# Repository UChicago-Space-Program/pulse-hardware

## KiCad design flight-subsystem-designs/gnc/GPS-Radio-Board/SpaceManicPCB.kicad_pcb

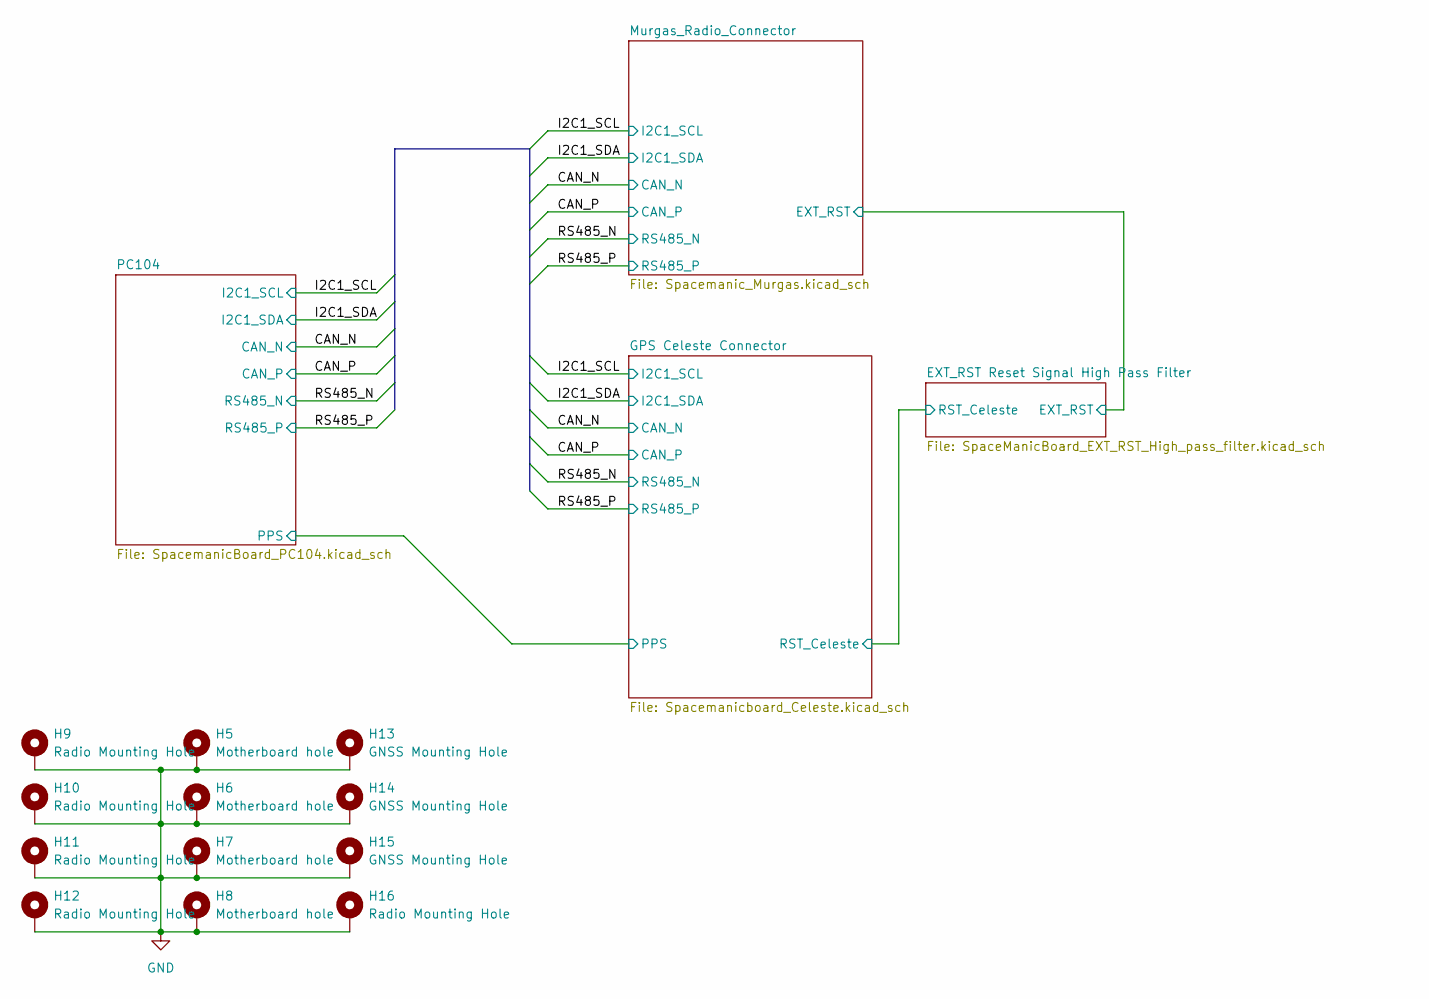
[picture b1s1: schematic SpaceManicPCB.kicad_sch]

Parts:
H5, H6, H7, H8: Motherboard hole; MountingHole_3.2mm_M3_DIN965_Pad_TopBottom
H9, H10, H11, H12, H16: Radio Mounting Hole; MountingHole_2.5mm
H13, H14, H15: GNSS Mounting Hole; MountingHole_2.5mm

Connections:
GND: H5.1, H6.1, H7.1, H8.1, H9.1, H10.1, H11.1, H12.1, H13.1, H14.1, H15.1, H16.1; also elsewhere on the board

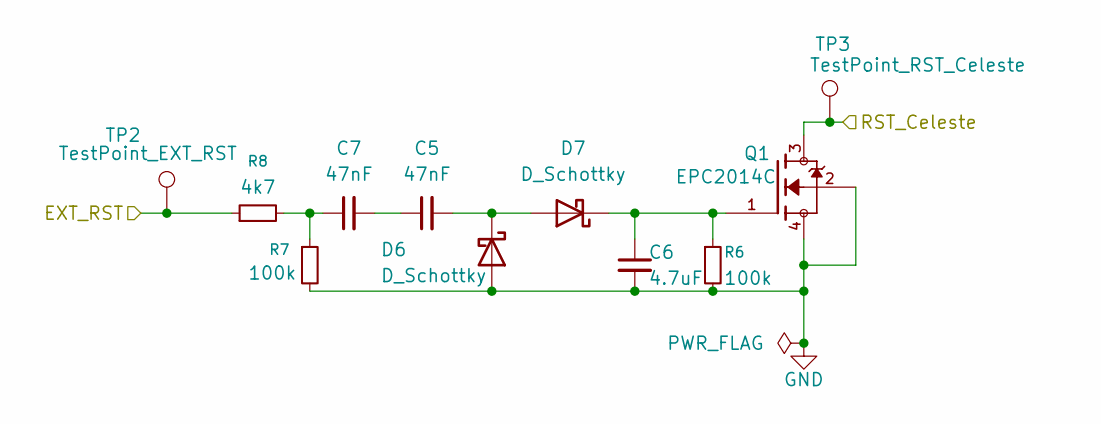
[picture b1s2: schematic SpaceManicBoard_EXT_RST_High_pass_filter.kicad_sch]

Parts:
C5, C7: 47nF; C_0603_1608Metric
C6: 4.7uF; C_0603_1608Metric
D6, D7: D_Schottky; D_0402_1005Metric
Q1: EPC2014C; TRANS_EPC2014C; PARTREV N/A
R6, R7: 100k; R_0603_1608Metric
R8: 4k7; R_0402_1005Metric
TP2: TestPoint_EXT_RST; TestPoint_Pad_D1.5mm
TP3: TestPoint_RST_Celeste; TestPoint_Pad_D1.5mm

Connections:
/EXT_RST Reset Signal High Pass Filter/EXT_RST: R8.1, TP2.1; also elsewhere on the board
/EXT_RST Reset Signal High Pass Filter/RST_Celeste: Q1.3, Q1.5, TP3.1; also elsewhere on the board
GND: C6.2, D6.2 (A), Q1.2, Q1.4, R6.2, R7.2; also elsewhere on the board
unnamed: C5.1, C7.2
unnamed: C7.1, R7.1, R8.2
unnamed: C5.2, D6.1 (K), D7.2 (A)
unnamed: C6.1, D7.1 (K), Q1.1, R6.1

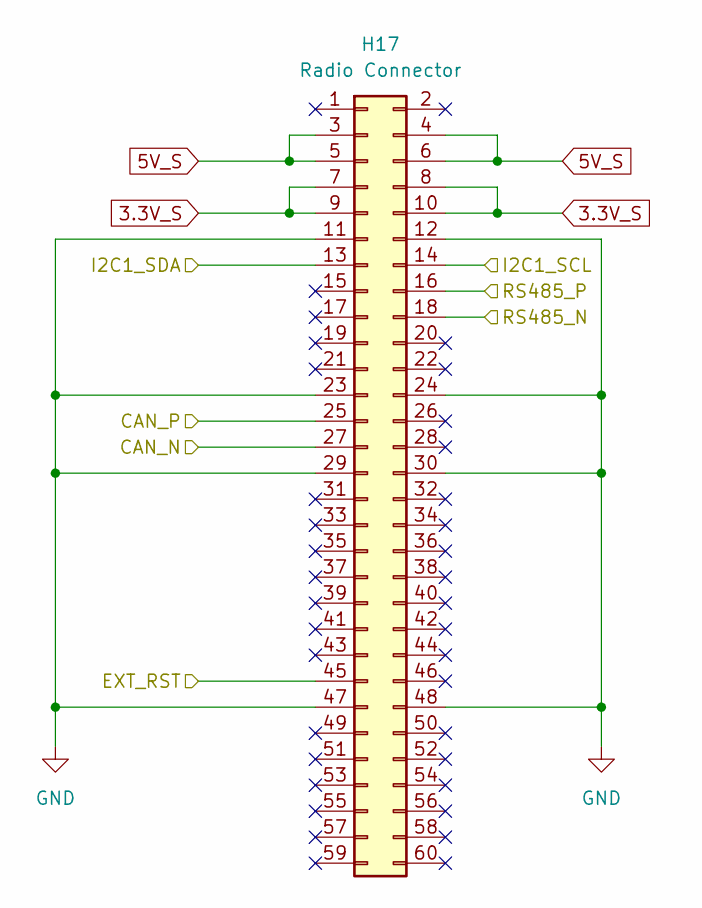
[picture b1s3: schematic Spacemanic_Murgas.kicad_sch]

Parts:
H17: Radio Connector; CON_MolexSlimStack_54363-0689

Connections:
3.3V_S: H17.7, H17.8, H17.9, H17.10; also elsewhere on the board
5V_S: H17.3, H17.4, H17.5, H17.6; also elsewhere on the board
/CAN_N: H17.27; also elsewhere on the board
/CAN_P: H17.25; also elsewhere on the board
/EXT_RST Reset Signal High Pass Filter/EXT_RST: H17.45; also elsewhere on the board
/I2C1_SCL: H17.14; also elsewhere on the board
/I2C1_SDA: H17.13; also elsewhere on the board
/RS485_N: H17.18; also elsewhere on the board
/RS485_P: H17.16; also elsewhere on the board
GND: H17.11, H17.12, H17.23, H17.24, H17.29, H17.30, H17.47, H17.48; also elsewhere on the board

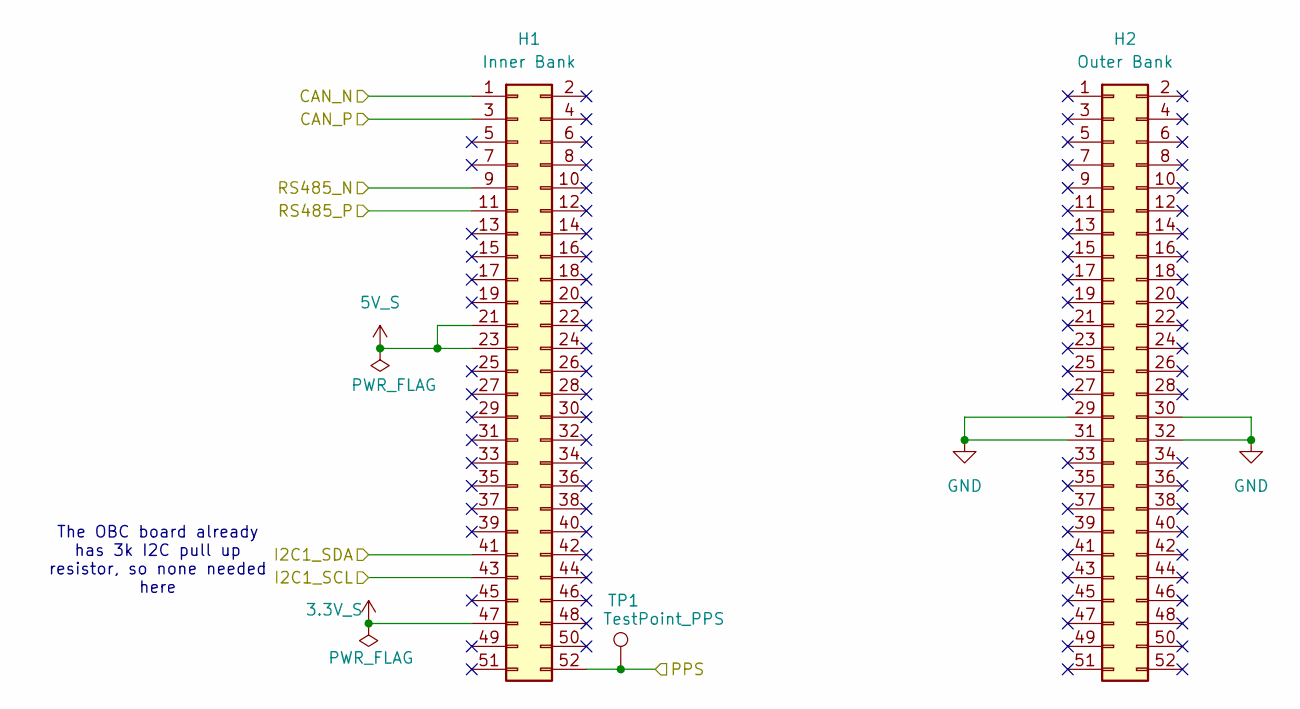
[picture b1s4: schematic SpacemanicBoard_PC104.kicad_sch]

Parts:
H1: Inner Bank; PinHeader_2x26_P2.54mm_Vertical
H2: Outer Bank; PinHeader_2x26_P2.54mm_Vertical
TP1: TestPoint_PPS; TestPoint_Pad_D1.5mm

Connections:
3.3V_S: H1.47; also elsewhere on the board
5V_S: H1.21, H1.23; also elsewhere on the board
/CAN_N: H1.1; also elsewhere on the board
/CAN_P: H1.3; also elsewhere on the board
/GPS Celeste Connector/PPS: H1.52, TP1.1; also elsewhere on the board
/I2C1_SCL: H1.43; also elsewhere on the board
/I2C1_SDA: H1.41; also elsewhere on the board
/RS485_N: H1.9; also elsewhere on the board
/RS485_P: H1.11; also elsewhere on the board
GND: H2.29, H2.30, H2.31, H2.32; also elsewhere on the board

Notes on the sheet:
The OBC board already has 3k I2C pull up resistor, so none needed here

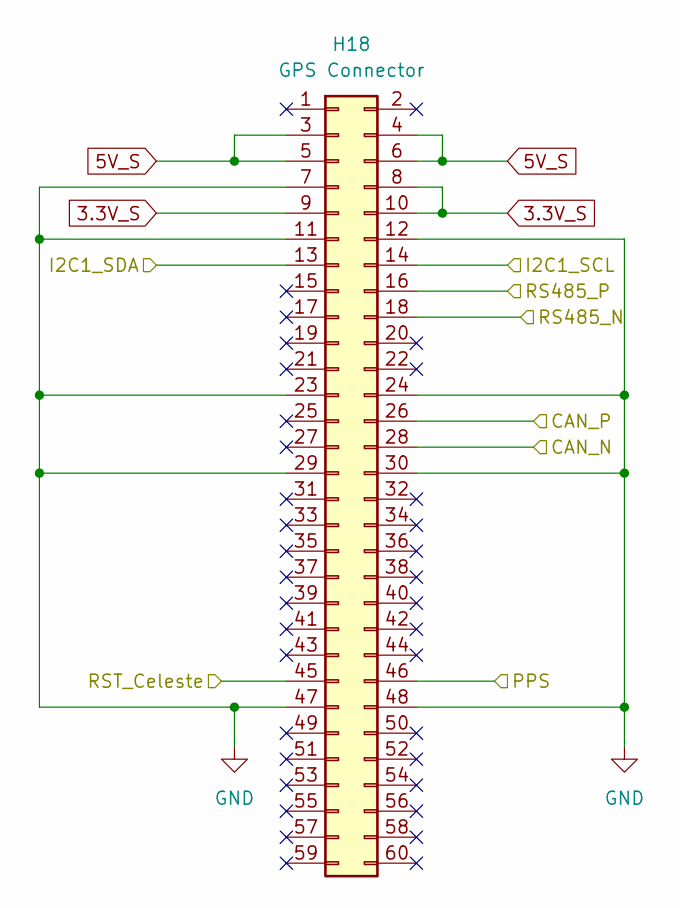
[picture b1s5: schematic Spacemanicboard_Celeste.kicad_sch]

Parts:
H18: GPS Connector; CON_MolexSlimStack_54363-0689

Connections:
3.3V_S: H18.8, H18.9, H18.10; also elsewhere on the board
5V_S: H18.3, H18.4, H18.5, H18.6; also elsewhere on the board
/CAN_N: H18.28; also elsewhere on the board
/CAN_P: H18.26; also elsewhere on the board
/EXT_RST Reset Signal High Pass Filter/RST_Celeste: H18.45; also elsewhere on the board
/GPS Celeste Connector/PPS: H18.46; also elsewhere on the board
/I2C1_SCL: H18.14; also elsewhere on the board
/I2C1_SDA: H18.13; also elsewhere on the board
/RS485_N: H18.18; also elsewhere on the board
/RS485_P: H18.16; also elsewhere on the board
GND: H18.7, H18.11, H18.12, H18.23, H18.24, H18.29, H18.30, H18.47, H18.48; also elsewhere on the board

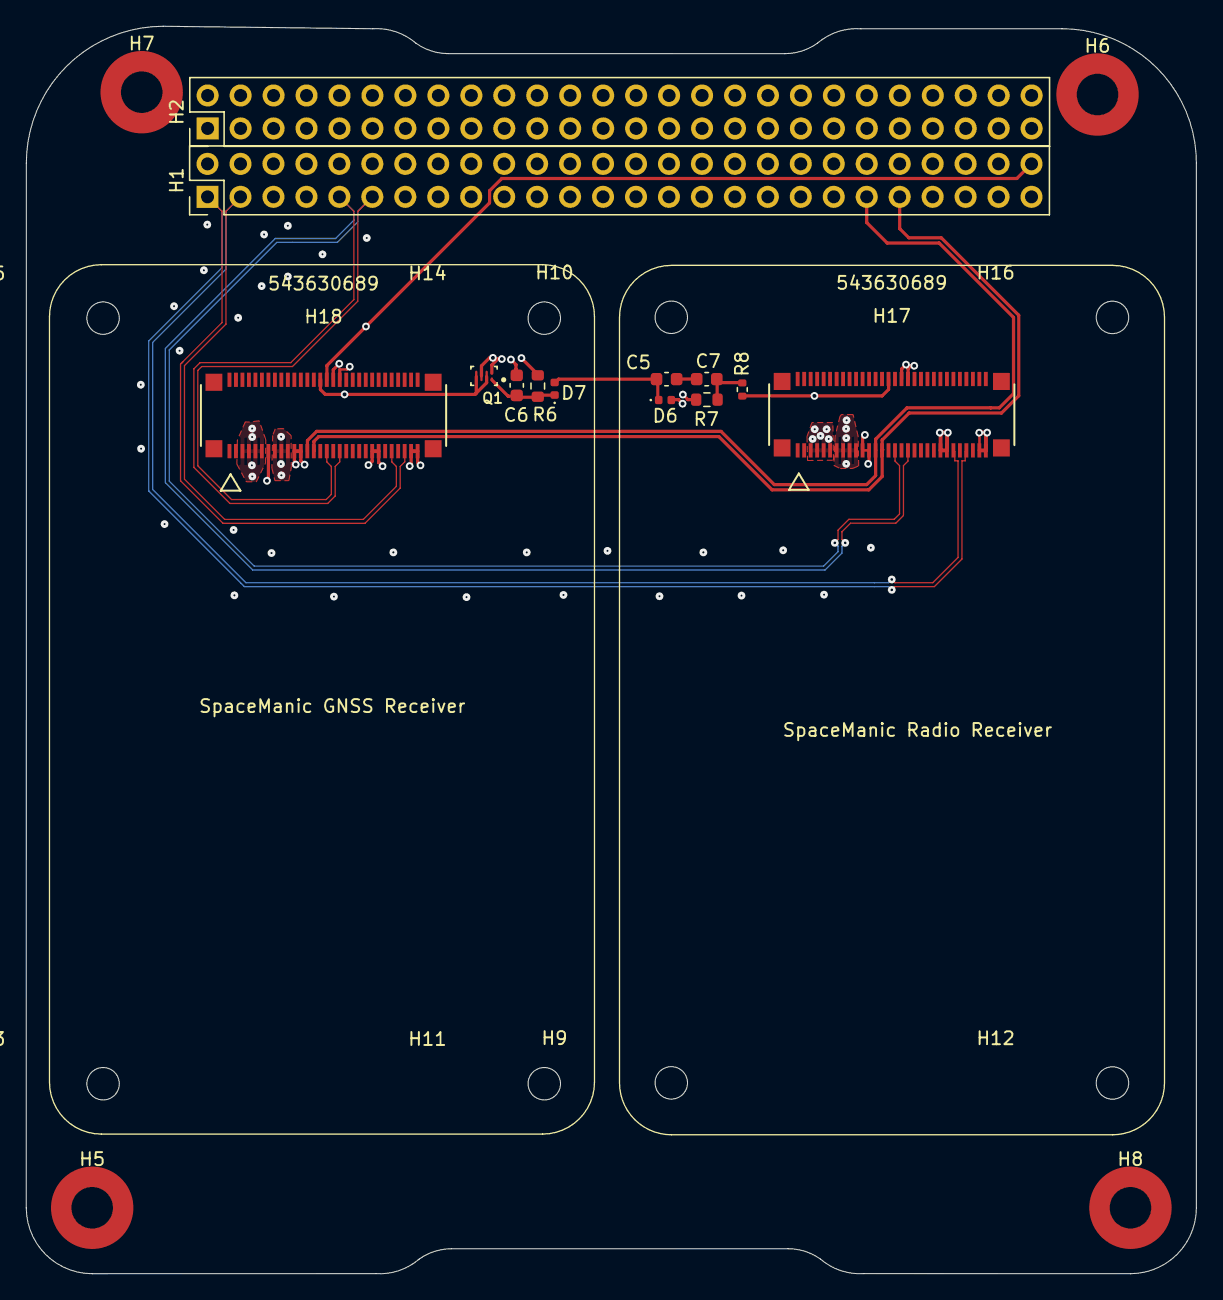
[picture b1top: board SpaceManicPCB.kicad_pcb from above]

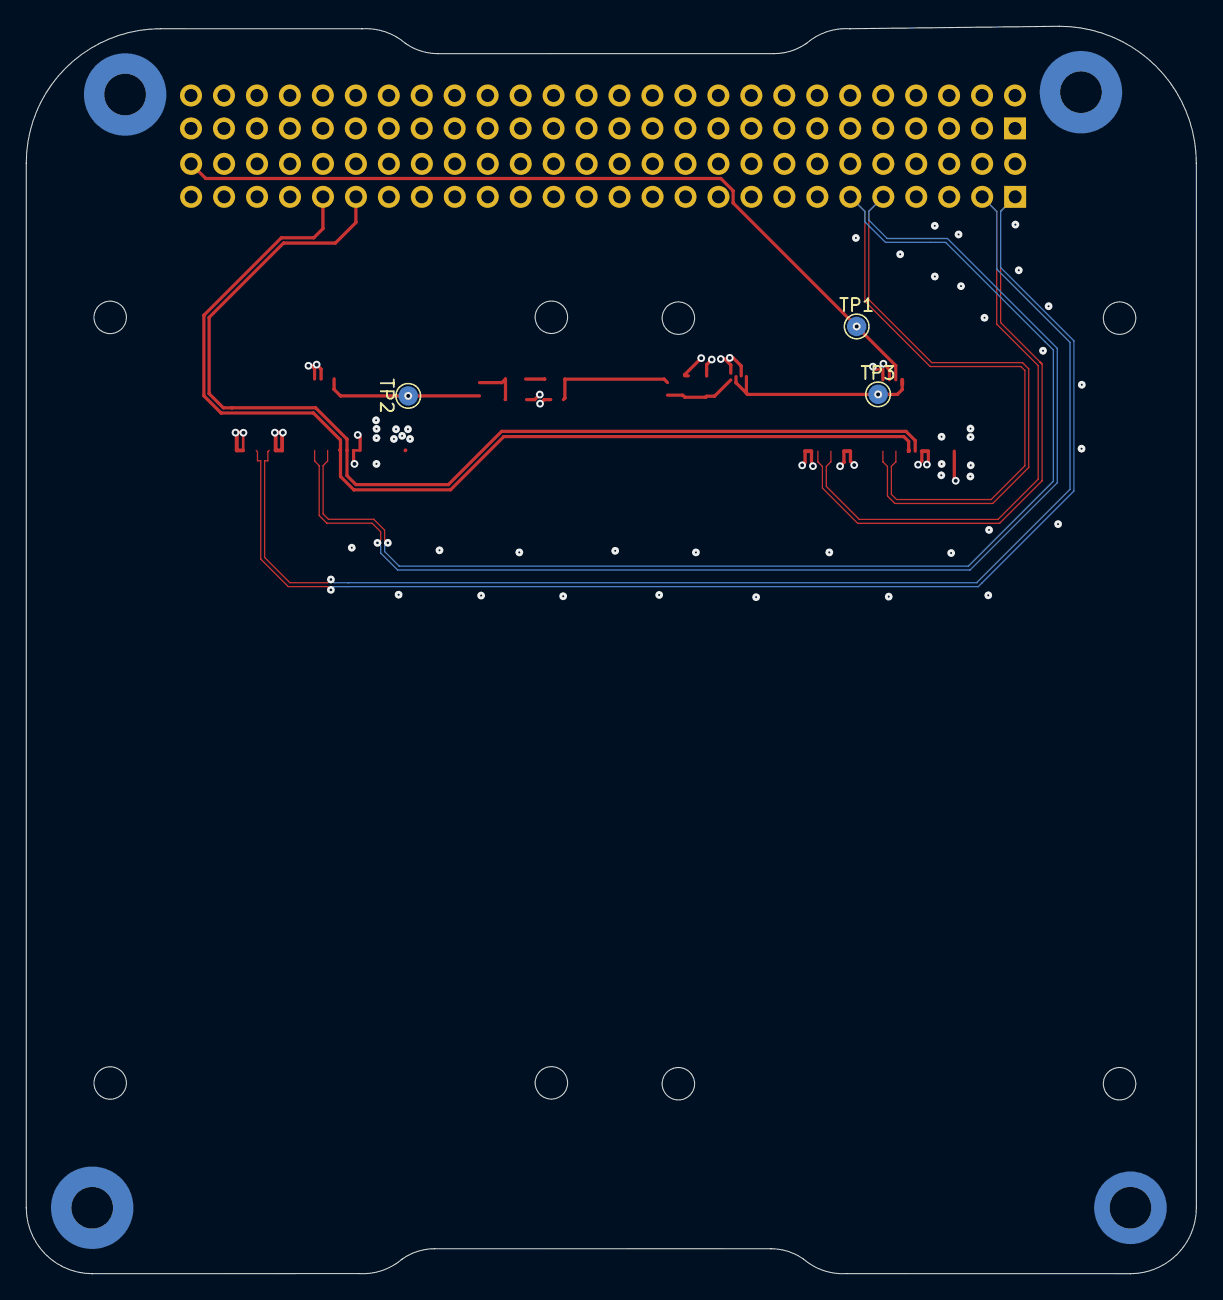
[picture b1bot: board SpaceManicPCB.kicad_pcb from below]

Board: 4 copper layers, 90.2 x 96.1 mm, 28 parts (3 on the bottom side), 16 nets.

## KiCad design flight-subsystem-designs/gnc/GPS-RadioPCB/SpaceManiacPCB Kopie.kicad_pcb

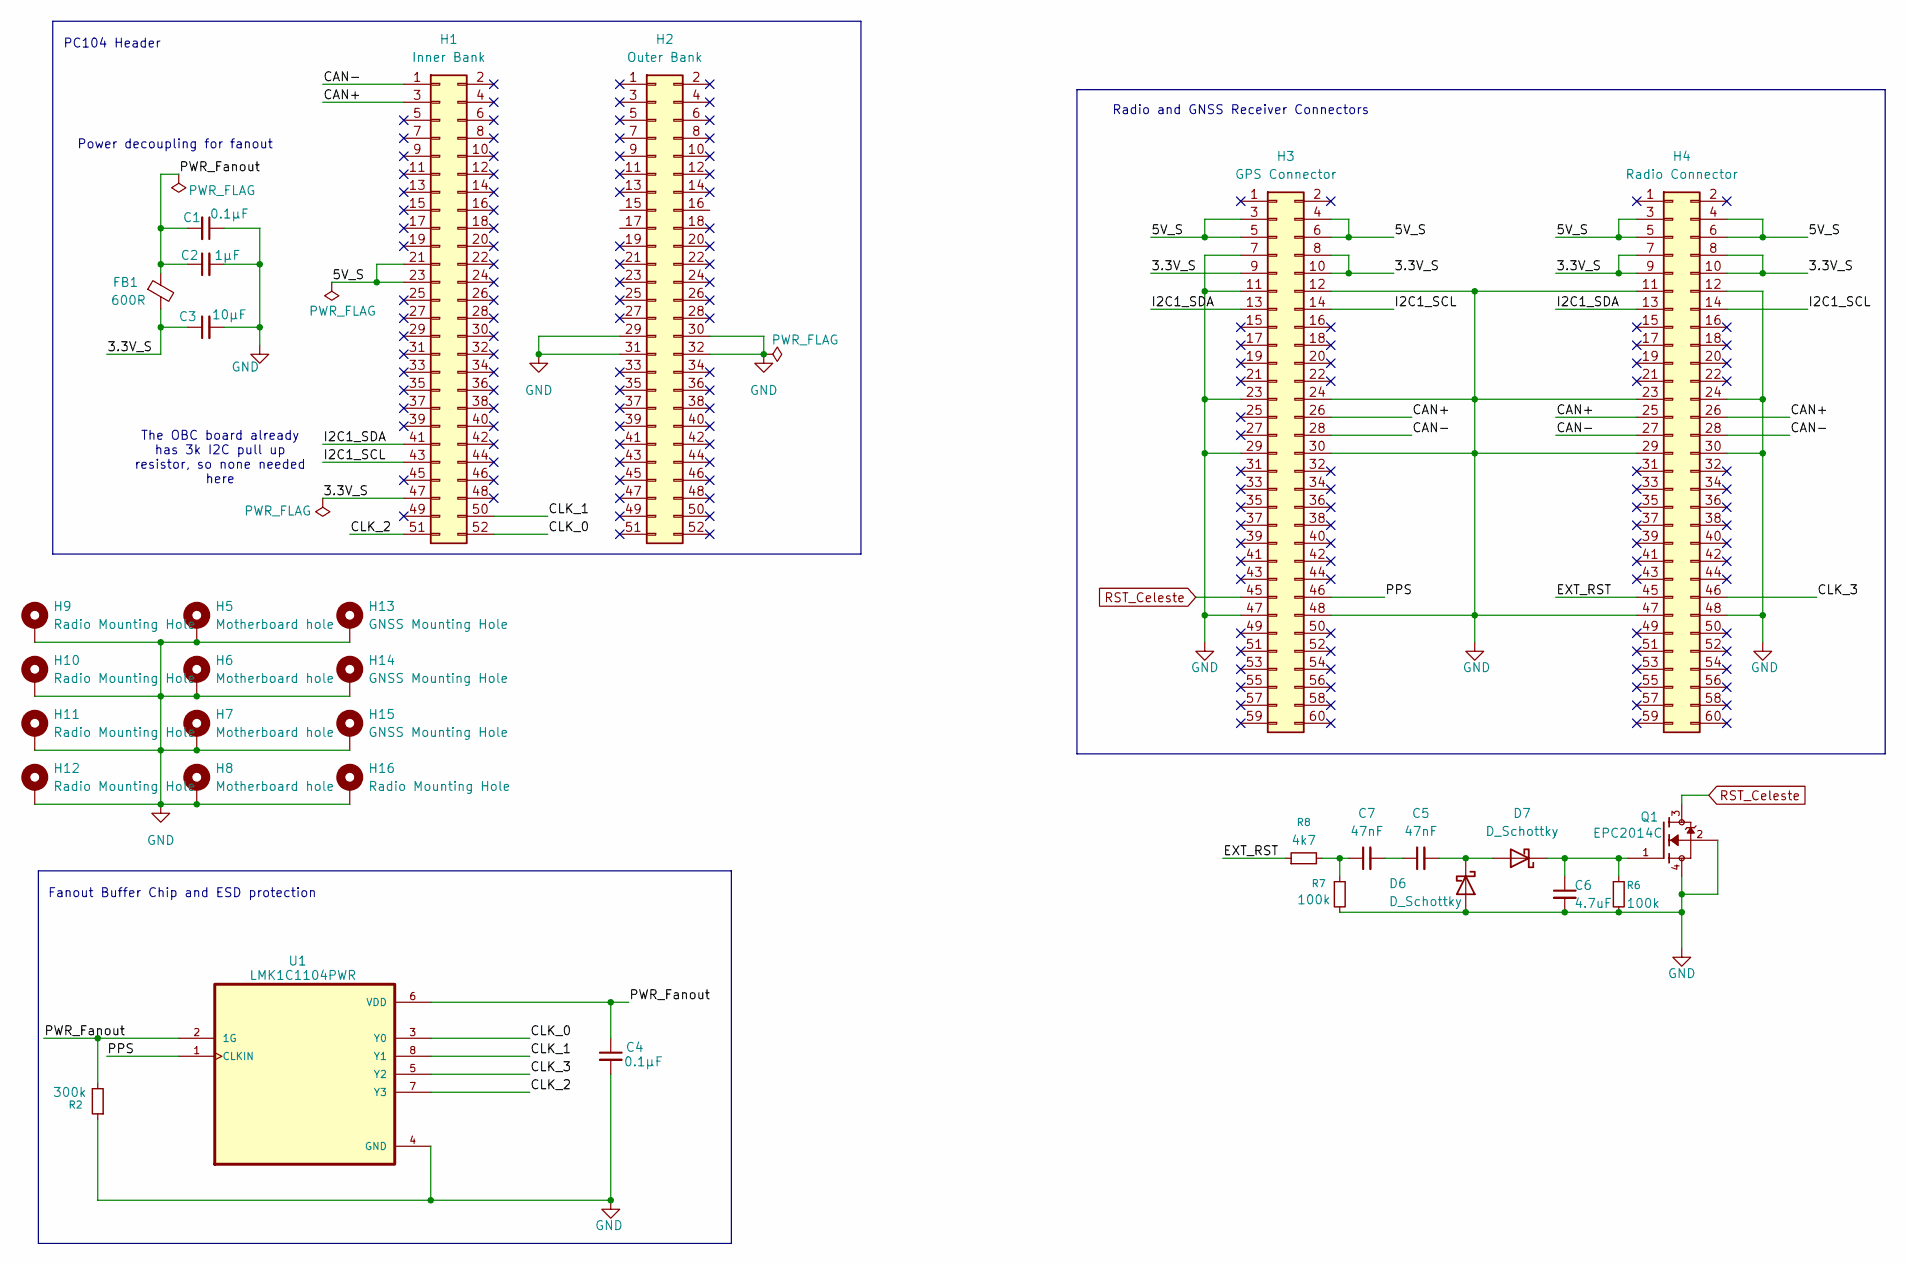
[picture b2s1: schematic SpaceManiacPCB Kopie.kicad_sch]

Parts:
C1, C4: 0.1μF; C_0402_1005Metric
C2: 1μF; C_0402_1005Metric
C3: 10μF; C_0402_1005Metric
C5, C7: 47nF; C_0603_1608Metric
C6: 4.7uF; C_0603_1608Metric
D6, D7: D_Schottky; D_0402_1005Metric
FB1: 600R; L_0603_1608Metric
H1: Inner Bank; PinHeader_2x26_P2.54mm_Vertical
H2: Outer Bank; PinHeader_2x26_P2.54mm_Vertical
H3: GPS Connector; CON_MolexSlimStack_54363-0689
H4: Radio Connector; CON_MolexSlimStack_54363-0689
H5, H6, H7, H8: Motherboard hole; MountingHole_3.2mm_M3_DIN965_Pad_TopBottom
H9, H10, H11, H12, H16: Radio Mounting Hole; MountingHole_3.2mm_M3_DIN965_Pad_TopBottom
H13, H14, H15: GNSS Mounting Hole; MountingHole_3.2mm_M3_DIN965_Pad_TopBottom
Q1: EPC2014C; TRANS_EPC2014C; PARTREV N/A
R2: 300k; R_0402_1005Metric
R6, R7: 100k; R_0402_1005Metric
R8: 4k7; R_0402_1005Metric
U1: LMK1C1104PWR; SOP65P640X120-8N; DigiKey_Part_Number 296-LMK1C1104PWRTR-ND

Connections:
/3.3V_S: C3.1, FB1.2, H1.47, H3.8, H3.9, H3.10, H4.7, H4.8, H4.9, H4.10
/5V_S: H1.21, H1.23, H3.3, H3.4, H3.5, H3.6, H4.3, H4.4, H4.5, H4.6
/CAN+: H1.3, H3.26, H4.25, H4.26
/CAN-: H1.1, H3.28, H4.27, H4.28
/CLK_0: H1.52, U1.3 (Y0)
/CLK_1: H1.50, U1.8 (Y1)
/CLK_2: H1.51, U1.7 (Y3)
/CLK_3: H4.46, U1.5 (Y2)
/EXT_RST: H4.45, R8.1
/I2C1_SCL: H1.43, H3.14, H4.14
/I2C1_SDA: H1.41, H3.13, H4.13
/PPS: H3.46, U1.1 (CLKIN)
/PWR_Fanout: C1.2, C2.1, C4.1, FB1.1, R2.2, U1.2 (1G), U1.6 (VDD)
GND: C1.1, C2.2, C3.2, C4.2, C6.2, D6.2 (A), H2.29, H2.30, H2.31, H2.32, H3.7, H3.11, H3.12, H3.23, H3.24, H3.29, H3.30, H3.47, H3.48, H4.11, H4.12, H4.23, H4.24, H4.29, H4.30, H4.47, H4.48, H5.1, H6.1, H7.1, H8.1, H9.1, H10.1, H11.1, H12.1, H13.1, H14.1, H15.1, H16.1, Q1.2, Q1.4, R2.1, R6.2, R7.2, U1.4 (GND)
unnamed: C5.1, C7.2
unnamed: C7.1, R7.1, R8.2
unnamed: C5.2, D6.1 (K), D7.2 (A)
unnamed: C6.1, D7.1 (K), Q1.1, R6.1
RST_Celeste: H3.45, Q1.3, Q1.5

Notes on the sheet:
PC104 Header
The OBC board already has 3k I2C pull up resistor, so none needed here
Fanout Buffer Chip and ESD protection
Power decoupling for fanout
Radio and GNSS Receiver Connectors

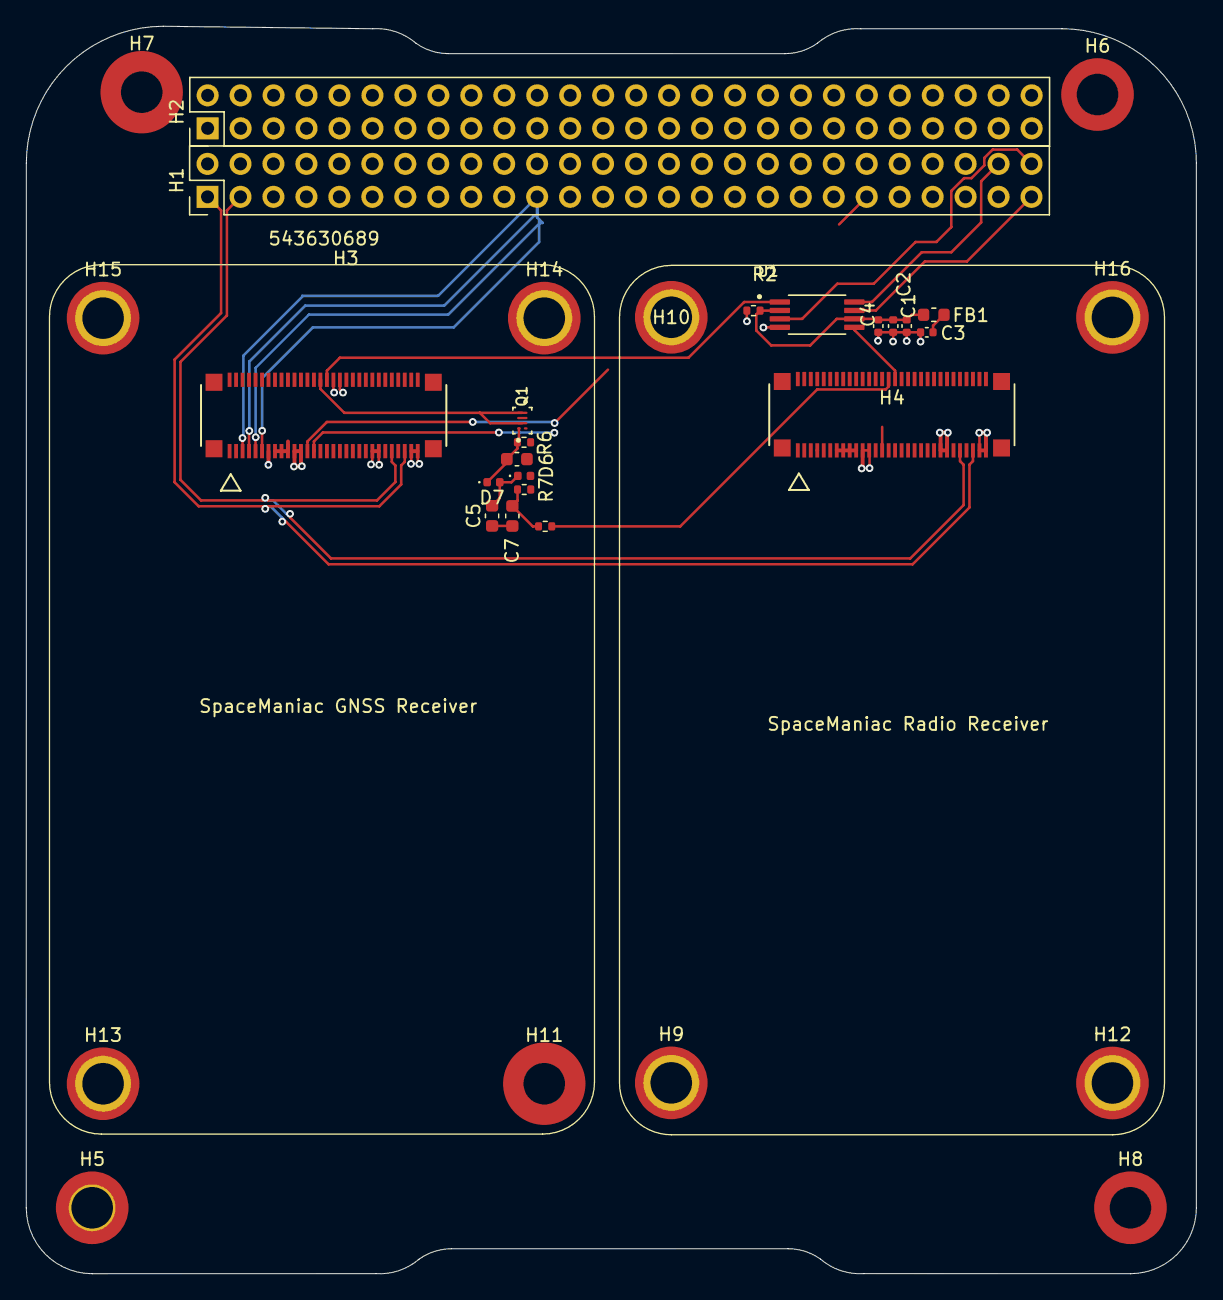
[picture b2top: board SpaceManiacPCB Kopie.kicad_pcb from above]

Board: 2 copper layers, 90.2 x 96.1 mm, 32 parts (0 on the bottom side), 19 nets.

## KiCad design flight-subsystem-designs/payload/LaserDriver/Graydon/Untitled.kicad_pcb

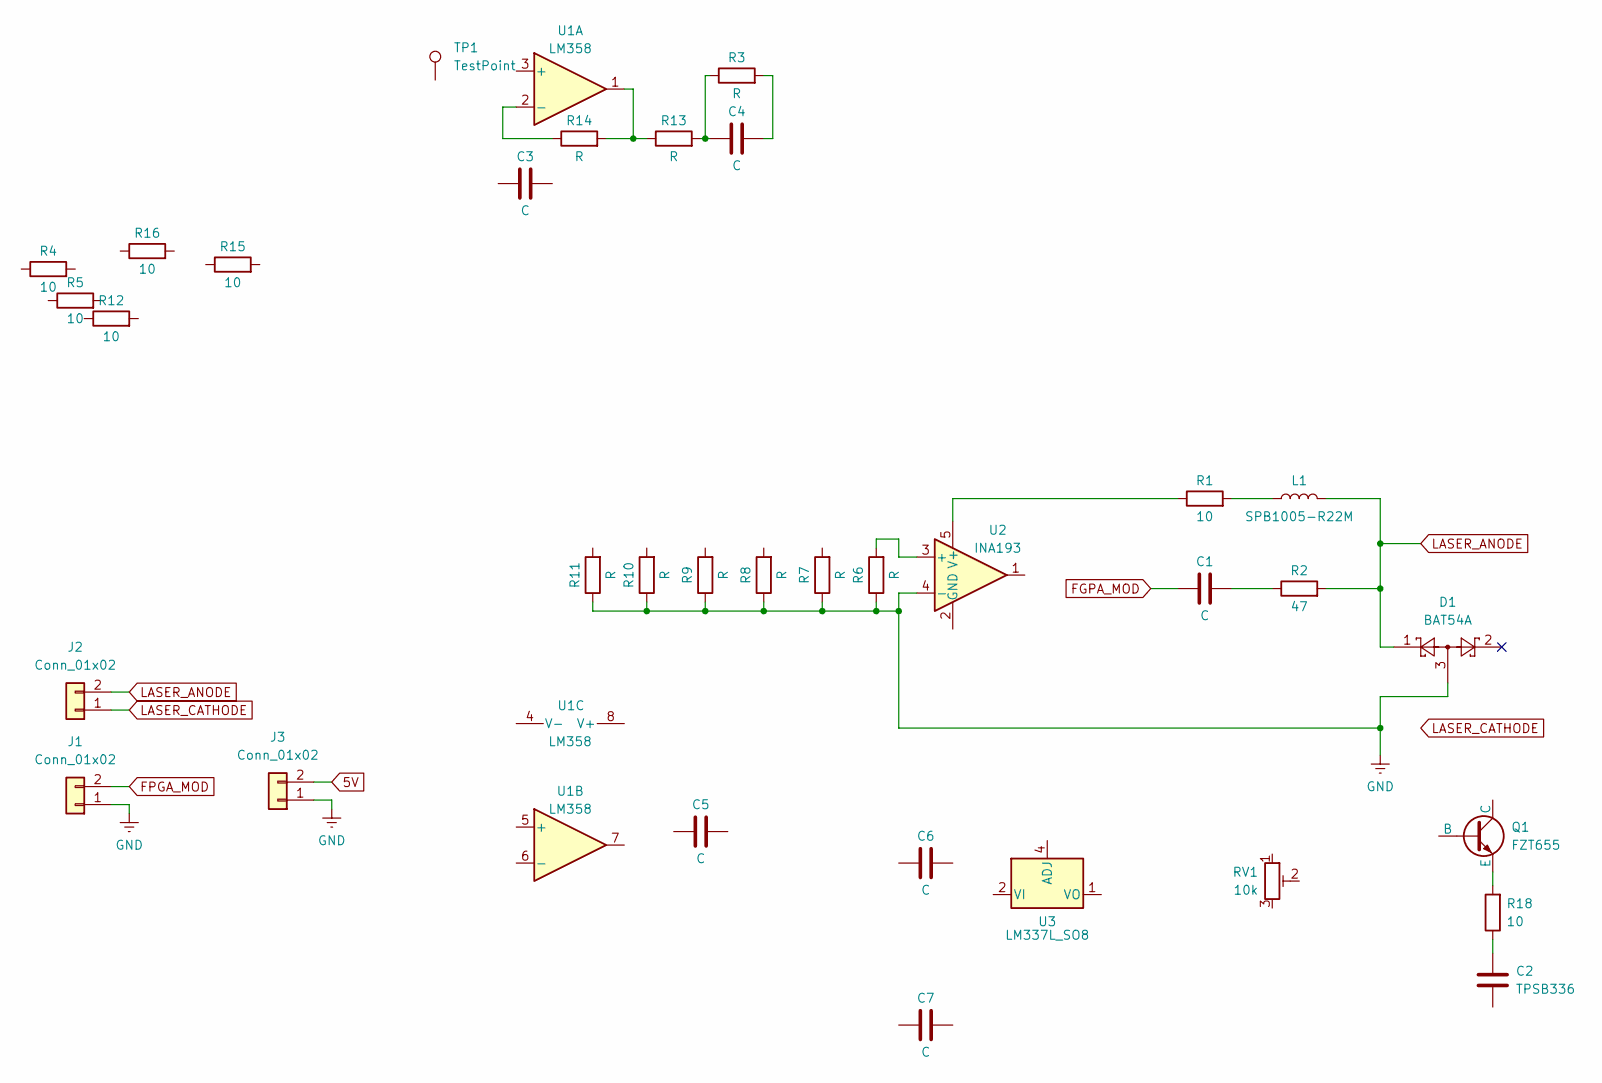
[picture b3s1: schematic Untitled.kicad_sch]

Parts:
C1, C3, C4, C5, C6, C7: C; C_0805_2012Metric
C2: TPSB336; C_1210_3225Metric
D1: BAT54A; SOT-23
J1, J2, J3: Conn_01x02; TerminalBlock_MetzConnect_Type073_RT02602HBLU_1x02_P5.08mm_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
L1: SPB1005-R22M
Q1: FZT655; SOT-223
R1, R4, R5, R12, R15, R16: 10; R_0805_2012Metric
R2: 47; R_0805_2012Metric
R3, R6, R7, R8, R9, R10, R11, R13, R14: R; R_0805_2012Metric
R18: 10; R_2512_6332Metric
RV1: 10k; Potentiometer_Bourns_3296Z_Horizontal
TP1: TestPoint
U1: LM358; SOIC-8_3.9x4.9mm_P1.27mm
U2: INA193; SOT-23-5
U3: LM337L_SO8; SOIC-8_3.9x4.9mm_P1.27mm

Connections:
5V: J3.2
FGPA_MOD: C1.1
FPGA_MOD: J1.2
GND: D1.3, J1.1, J3.1, R6.1, R7.1, R8.1, R9.1, R10.1, R11.1, U2.4 (-)
LASER_ANODE: D1.1, J2.2, L1.2, R2.2
LASER_CATHODE: J2.1
unnamed: C1.2, R2.1
unnamed: C2.1, R18.1
unnamed: C4.1, R3.1, R13.2
unnamed: C4.2, R3.2
unnamed: L1.1, R1.2
unnamed: Q1.3 (E), R18.2
unnamed: R13.1, R14.2, U1.1
unnamed: R14.1, U1.2 (-)
unnamed: R6.2, U2.3 (+)
unnamed: R1.1, U2.5 (V+)
unnamed: U3.2 (VI), U3.3 (VI), U3.6 (VI), U3.7 (VI)

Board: 2 copper layers, 34 parts (0 on the bottom side), 13 nets, no tracks yet.

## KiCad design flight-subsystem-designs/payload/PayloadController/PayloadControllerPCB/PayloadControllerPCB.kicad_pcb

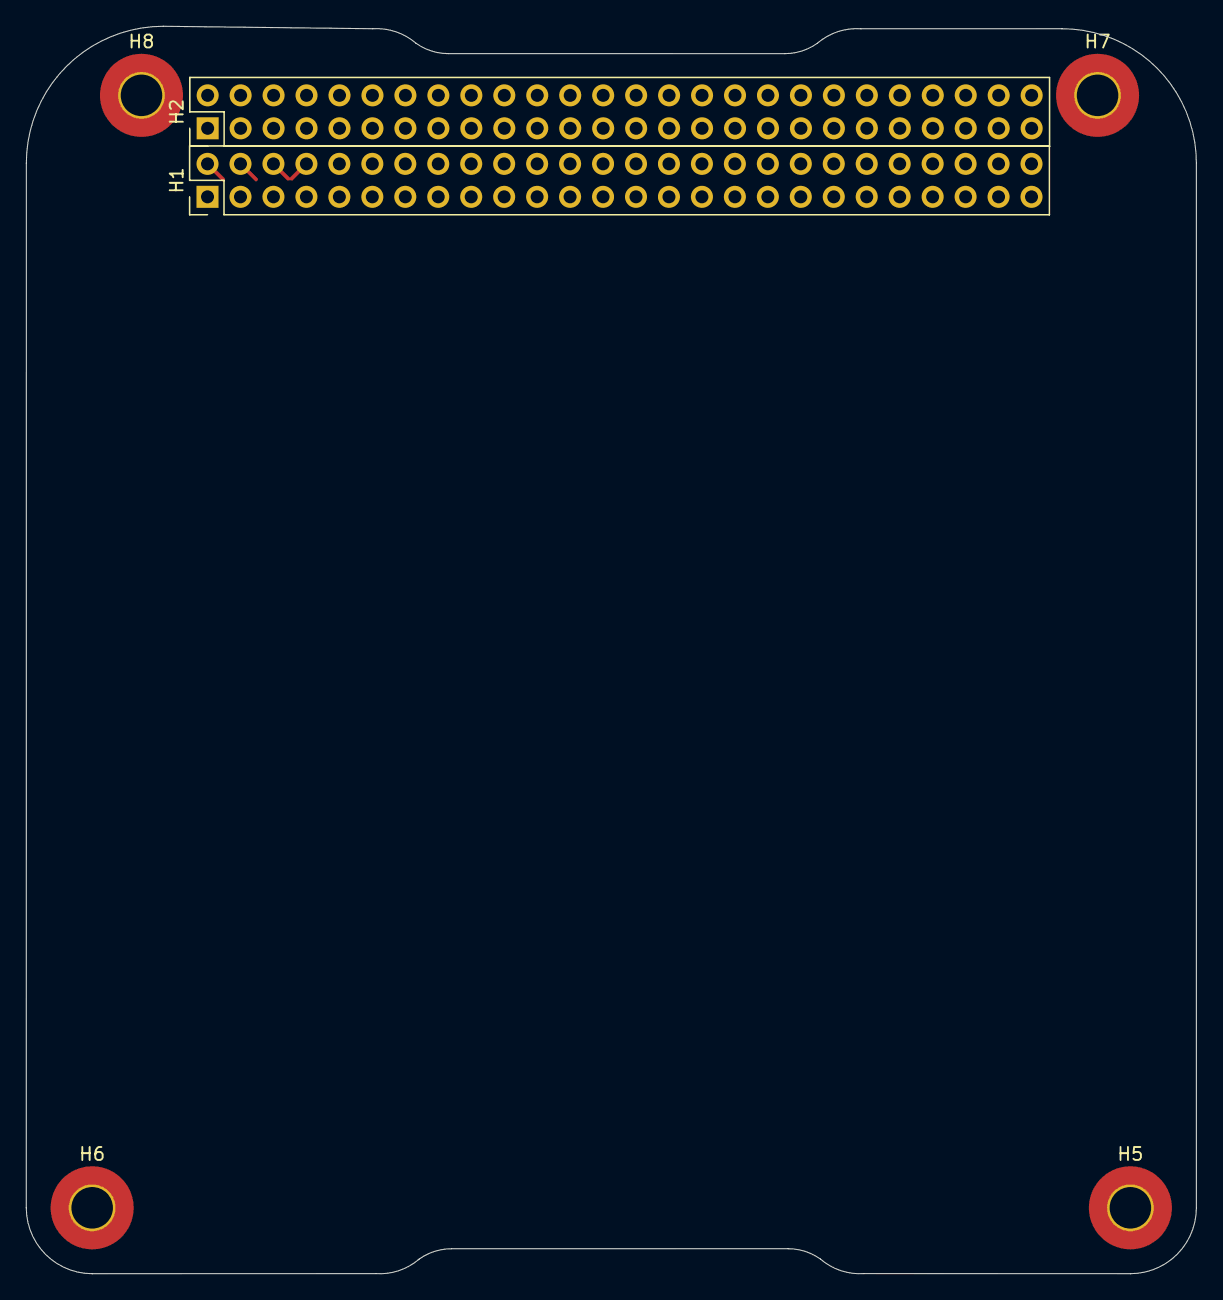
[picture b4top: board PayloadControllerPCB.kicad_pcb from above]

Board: 2 copper layers, 90.2 x 96.1 mm, 6 parts (0 on the bottom side), 3 nets.

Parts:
H1: Inner Bank; PinHeader_2x26_P2.54mm_Vertical
H2: Outer Bank; PinHeader_2x26_P2.54mm_Vertical
H5, H6, H7, H8: Motherboard Mounting Hole; MountingHole_3.2mm_M3_Pad_TopBottom

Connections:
5V_S: H1.21, H1.23
GND: H2.29, H2.30, H2.31, H2.32
RAW_BATT: H1.6, H1.8
